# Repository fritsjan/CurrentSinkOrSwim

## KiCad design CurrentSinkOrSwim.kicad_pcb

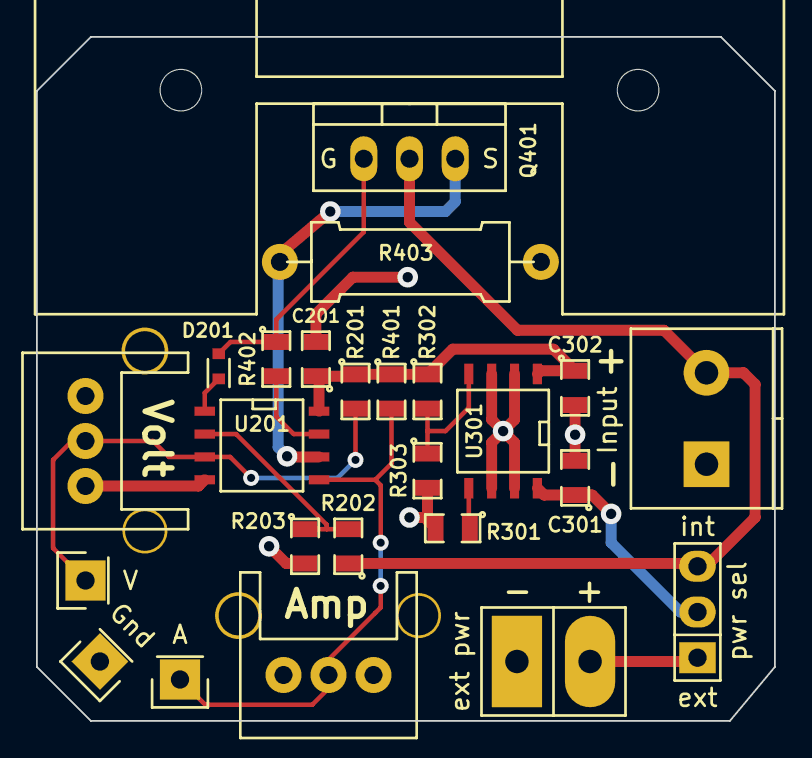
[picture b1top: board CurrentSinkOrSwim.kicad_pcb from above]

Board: 2 copper layers, 41.0 x 38.0 mm, 25 parts (0 on the bottom side), 14 nets.

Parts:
C201, C301, C302: C; SMD-0805
D201: DIODE; SOD-523
P1: CONN_01X01; FA-T220-38E
P2: V; Pin_Header_Straight_1x01
P3: A; Pin_Header_Straight_1x01
P4: Gnd; Pin_Header_Straight_1x01
P101: ext pwr; Pads-01x02
P102: pwr sel; Pin_Header_Straight_1x03
P103: Input; TB-01x02
Q401: BUK9575; current-TO-220_FET-GDS_Vertical
R201: 28.7K; SMD-0805
R202: 9K; SMD-0805
R203, R402: 1K; SMD-0805
R301: 0; SMD-0805
R302: 27K; SMD-0805
R303: 21.6K; SMD-0805
R401: 68K; SMD-0805
R403: .1; 1W-Resistor
RV201, RV401: 10K; P090L-02F25BR10K
U201: LMV358; SOIC-8-N
U301: LM2931D-R; SOIC-8-N

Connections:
2.7V: C201.1, C302.1, R201.1, R302.1, R401.1, U201.8, U301.1
/Current Control/Current_Sink+: P102.3, P103.2, Q401.D, R202.1
/Current Control/FET_Gate: D201.1, Q401.G, R402.1
/Power Regulation/Vin: C301.1, P102.2, U301.8
GND: C201.2, C301.2, C302.2, P4.1, P101.1, P103.1, R203.2, R301.2, R303.2, R403.2, RV201.3, RV401.3, U201.4, U301.2, U301.3, U301.6, U301.7
unnamed: D201.2, U201.1
unnamed: P2.1, R201.2, RV201.2, U201.3
unnamed: P3.1, R401.2, RV401.2, U201.5
unnamed: P101.2, P102.1
unnamed: Q401.S, R403.1, U201.6
unnamed: R202.2, R203.1, U201.2
unnamed: R301.1, U301.5
unnamed: R302.2, R303.1, U301.4
unnamed: R402.2, U201.7

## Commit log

2015-02-01 KiCad project and schematic creation
2015-02-01 Adding preliminary components (without values) to the schematic.
2015-02-09 Updating The Schematic With Part Numbers
2015-02-09 Finding A Higher Rated Linear Regulator
2015-02-10 Adding SPICE model and associated files
2015-02-10 Controlling The Power Burn op amp circuit.
2015-02-11 Breaking the schematic into hierarchical sheets and updating VoltageControl circuit
2015-02-13 Initial Annotation
2015-02-13 Preliminary association of components and placement into layout.
2015-02-14 Small changes after ERC check
2015-02-14 Created new footprint library and created a heatsink footprint.
2015-02-14 Adding .gitignore for bakcup and data files
2015-02-14 A few more ignored fies
2015-02-15 Added board outline
2015-02-16 Replacing the terminal block footprints
2015-02-16 Added new potentiometer footprints to layout
2015-02-16 Fixed divider resistors and found values
2015-02-16 Cosmetic cleanup of schematic
2015-02-18 Added keep out and did initial placement
2015-02-20 CSOS Layout session 1
2015-02-21 Moved pots/terms and routed traces to all components
2015-02-22 Ground fill and DRC
2015-02-22 Added graphic and text above heatsink
2015-02-25 Initial generation of gerber files
2015-02-26 Revised gerber files and zipped up for fabrication
2015-03-01 added measure pins and ripup layout
2015-03-01 Changed footprints, changed layout
2015-03-01 Routing done
2015-03-01 test netlist
2015-03-01 Revert "Routing done"
    This reverts commit 9c8e4a17aa7ae0fb22a7aeeae40aa608407b6119.
    Conflicts:
    CurrentSinkOrSwim.sch
2015-03-01 Routing done - Final
    Just add artwork
2015-03-02 Final done - Uploaded to OSHPark
